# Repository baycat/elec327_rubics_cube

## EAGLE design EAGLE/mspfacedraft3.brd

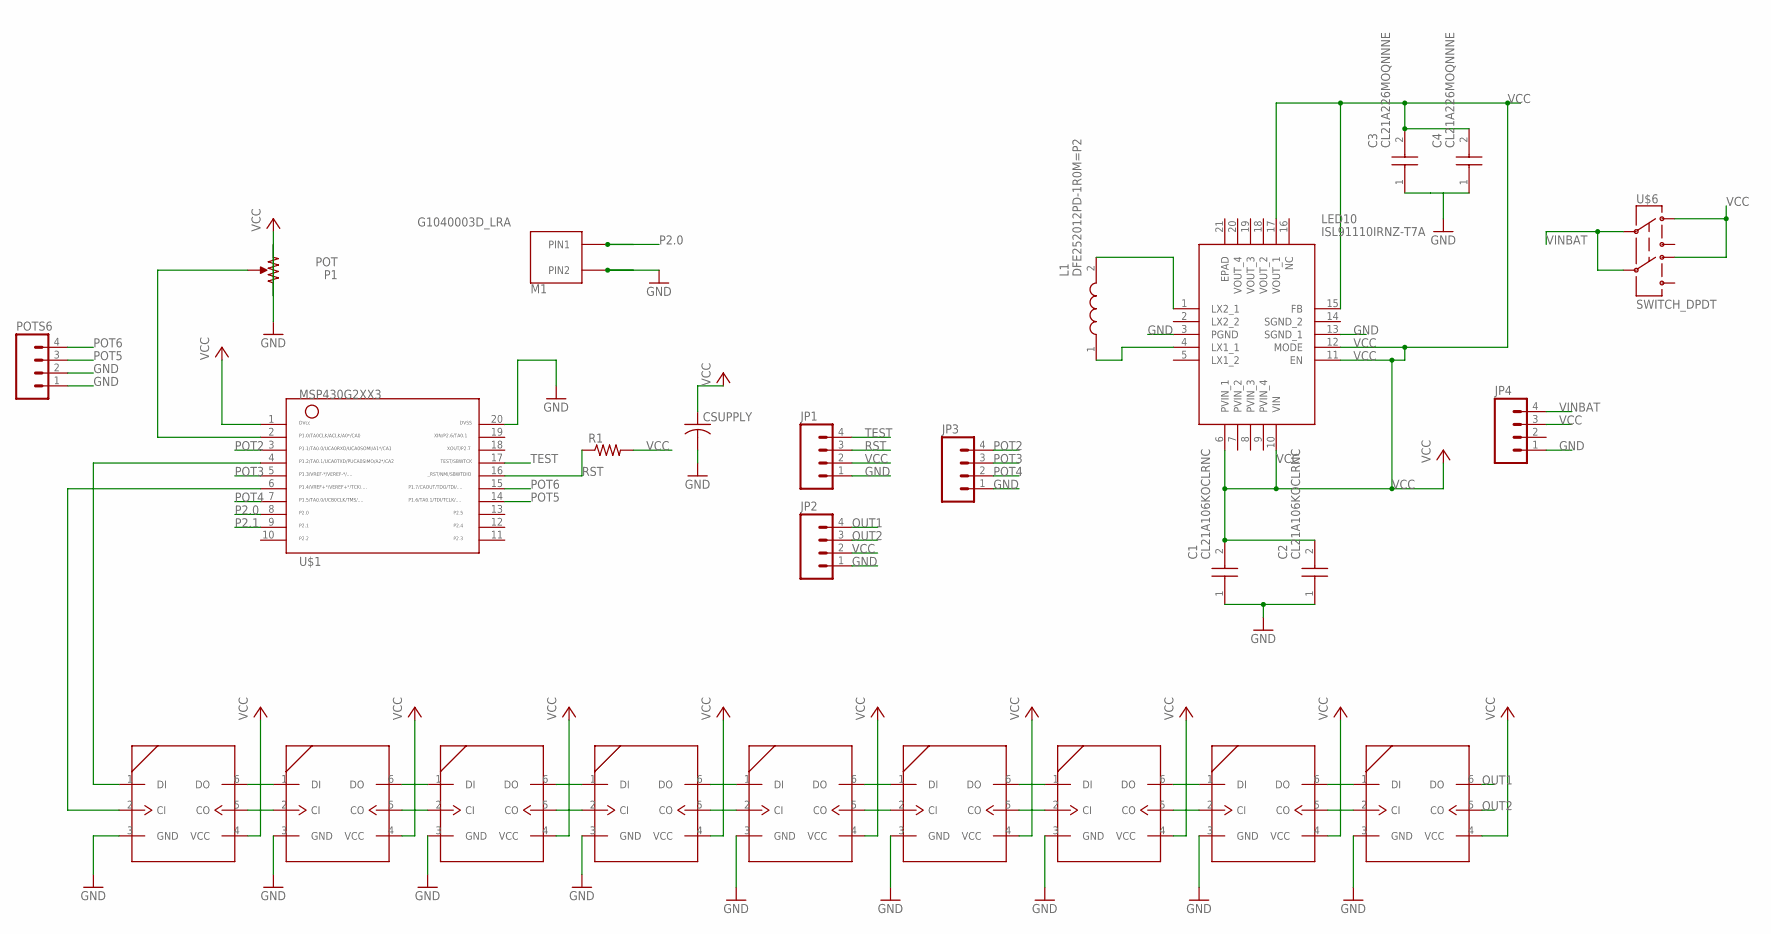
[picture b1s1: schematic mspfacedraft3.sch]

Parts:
C1, C2: CL21A106KOCLRNC; CAPC2012X95N
C3, C4: CL21A226MOQNNNE; CAPC2012X140N
CSUPPLY: C-USC1206; C1206
JP1, JP2, JP3, JP4: M04LOCK; 1X04_LOCK
L1: DFE252012PD-1R0M=P2; DFE2HCAH1R0MJ0L
LED1, LED2, LED3, LED4, LED5, LED6, LED7, LED8, LED9: APA102; 5050
LED10: ISL91110IRNZ-T7A; QFN50P400X400X100-21N
M1: G1040003D_LRA; COIN_VIBRATION_MOTOR
P1: POT
POTS6: M04LOCK; 1X04_LOCK
R1: R-US_R1206; R1206
U$1: MSP430G2XX3TSSOP; PW20
U$6: SWITCH_DPDT; JS_DPDT_TH

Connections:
GND: C1.1, C2.1, C3.1, C4.1, CSUPPLY.2, JP1.1, JP2.1, JP3.1, JP4.1, LED1.3 (GND), LED2.3 (GND), LED3.3 (GND), LED4.3 (GND), LED5.3 (GND), LED6.3 (GND), LED7.3 (GND), LED8.3 (GND), LED9.3 (GND), LED10.3 (PGND), LED10.13 (SGND_1), M1.P$2 (PIN2), P1.GND (CW), POTS6.1, POTS6.2, U$1.20
unnamed: LED1.6 (DO), LED2.1 (DI)
unnamed: LED1.5 (CO), LED2.2 (CI)
unnamed: LED2.6 (DO), LED3.1 (DI)
unnamed: LED2.5 (CO), LED3.2 (CI)
unnamed: LED3.6 (DO), LED4.1 (DI)
unnamed: LED3.5 (CO), LED4.2 (CI)
unnamed: LED1.1 (DI), U$1.4
unnamed: LED1.2 (CI), U$1.6
unnamed: LED4.6 (DO), LED5.1 (DI)
unnamed: LED4.5 (CO), LED5.2 (CI)
unnamed: LED5.6 (DO), LED6.1 (DI)
unnamed: LED5.5 (CO), LED6.2 (CI)
unnamed: LED6.6 (DO), LED7.1 (DI)
unnamed: LED6.5 (CO), LED7.2 (CI)
unnamed: LED7.6 (DO), LED8.1 (DI)
unnamed: LED7.5 (CO), LED8.2 (CI)
unnamed: LED8.6 (DO), LED9.1 (DI)
unnamed: LED8.5 (CO), LED9.2 (CI)
unnamed: L1.1, LED10.4 (LX1_1)
unnamed: P1.SIG (S), U$1.2
unnamed: L1.2, LED10.1 (LX2_1)
OUT1: JP2.4, LED9.6 (DO)
OUT2: JP2.3, LED9.5 (CO)
P2.0: M1.P$1 (PIN1), U$1.8
P2.1: U$1.9
POT2: JP3.4, U$1.3
POT3: JP3.3, U$1.5
POT4: JP3.2, U$1.7
POT5: POTS6.3, U$1.14
POT6: POTS6.4, U$1.15
RST: JP1.3, R1.1, U$1.16
TEST: JP1.4, U$1.17
VCC: C1.2, C2.2, C3.2, C4.2, CSUPPLY.1, JP1.2, JP2.2, JP4.3, LED1.4 (VCC), LED2.4 (VCC), LED3.4 (VCC), LED4.4 (VCC), LED5.4 (VCC), LED6.4 (VCC), LED7.4 (VCC), LED8.4 (VCC), LED9.4 (VCC), LED10.6 (PVIN_1), LED10.10 (VIN), LED10.11 (EN), LED10.12 (MODE), LED10.15 (FB), LED10.17 (VOUT_1), P1.VDD (CCW), R1.2, U$1.1, U$6.1, U$6.4
VINBAT: JP4.4, U$6.2, U$6.5

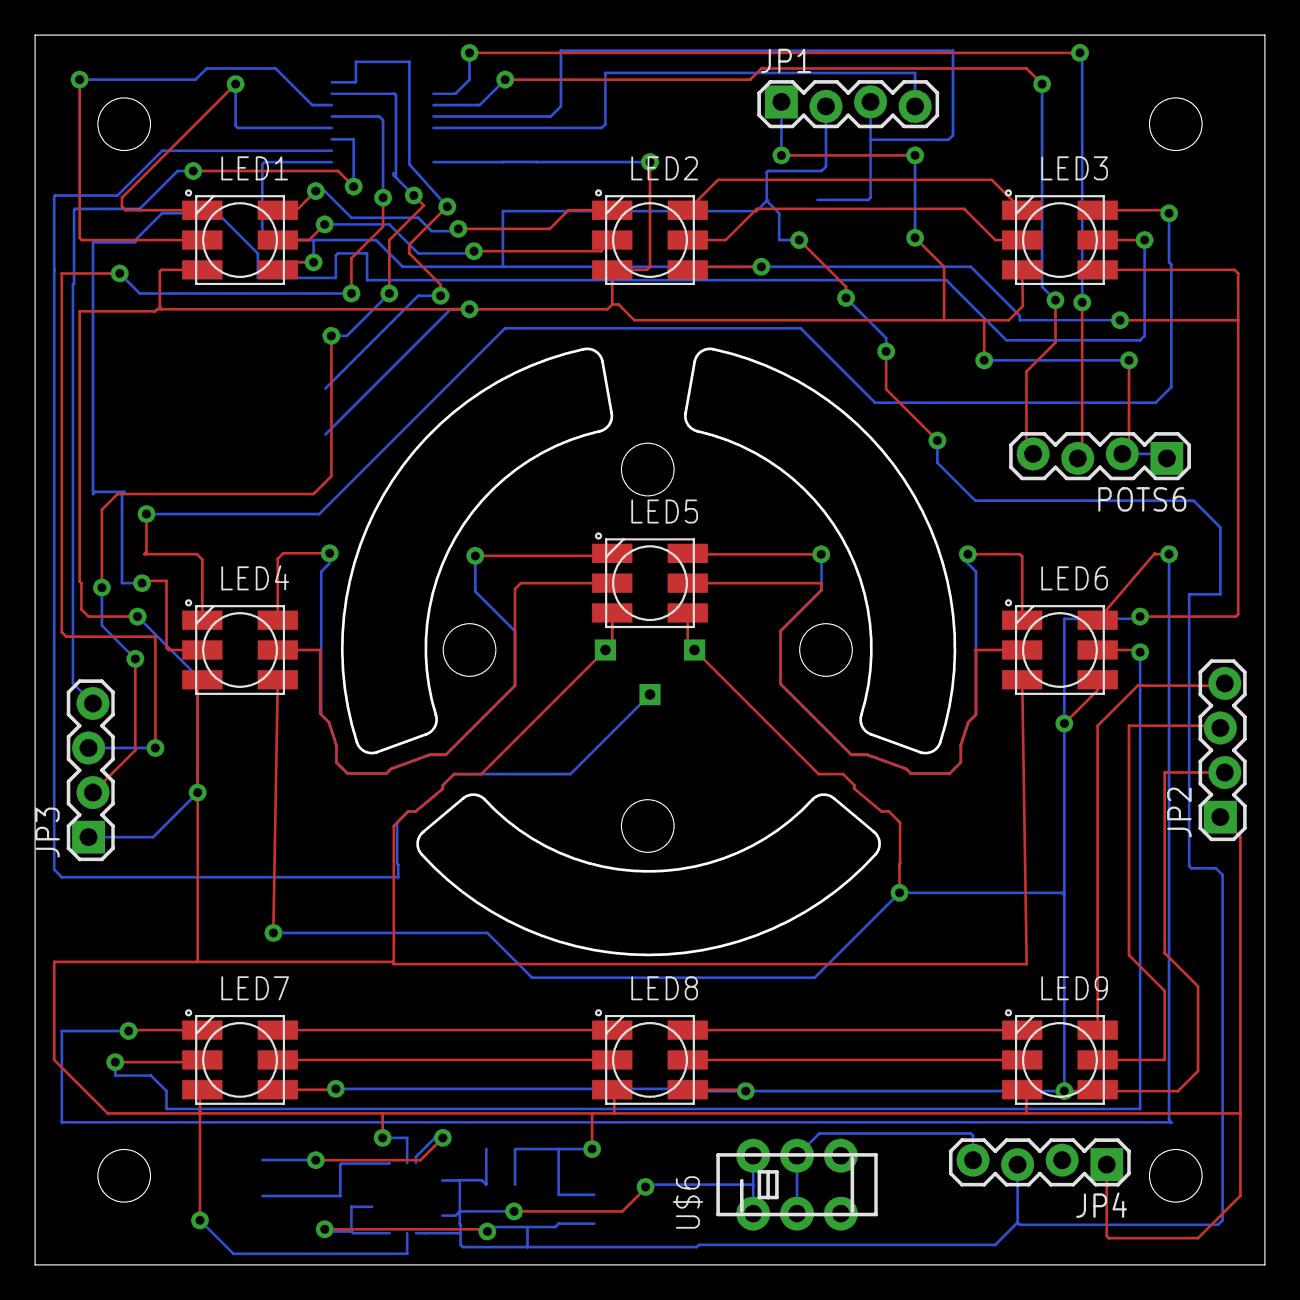
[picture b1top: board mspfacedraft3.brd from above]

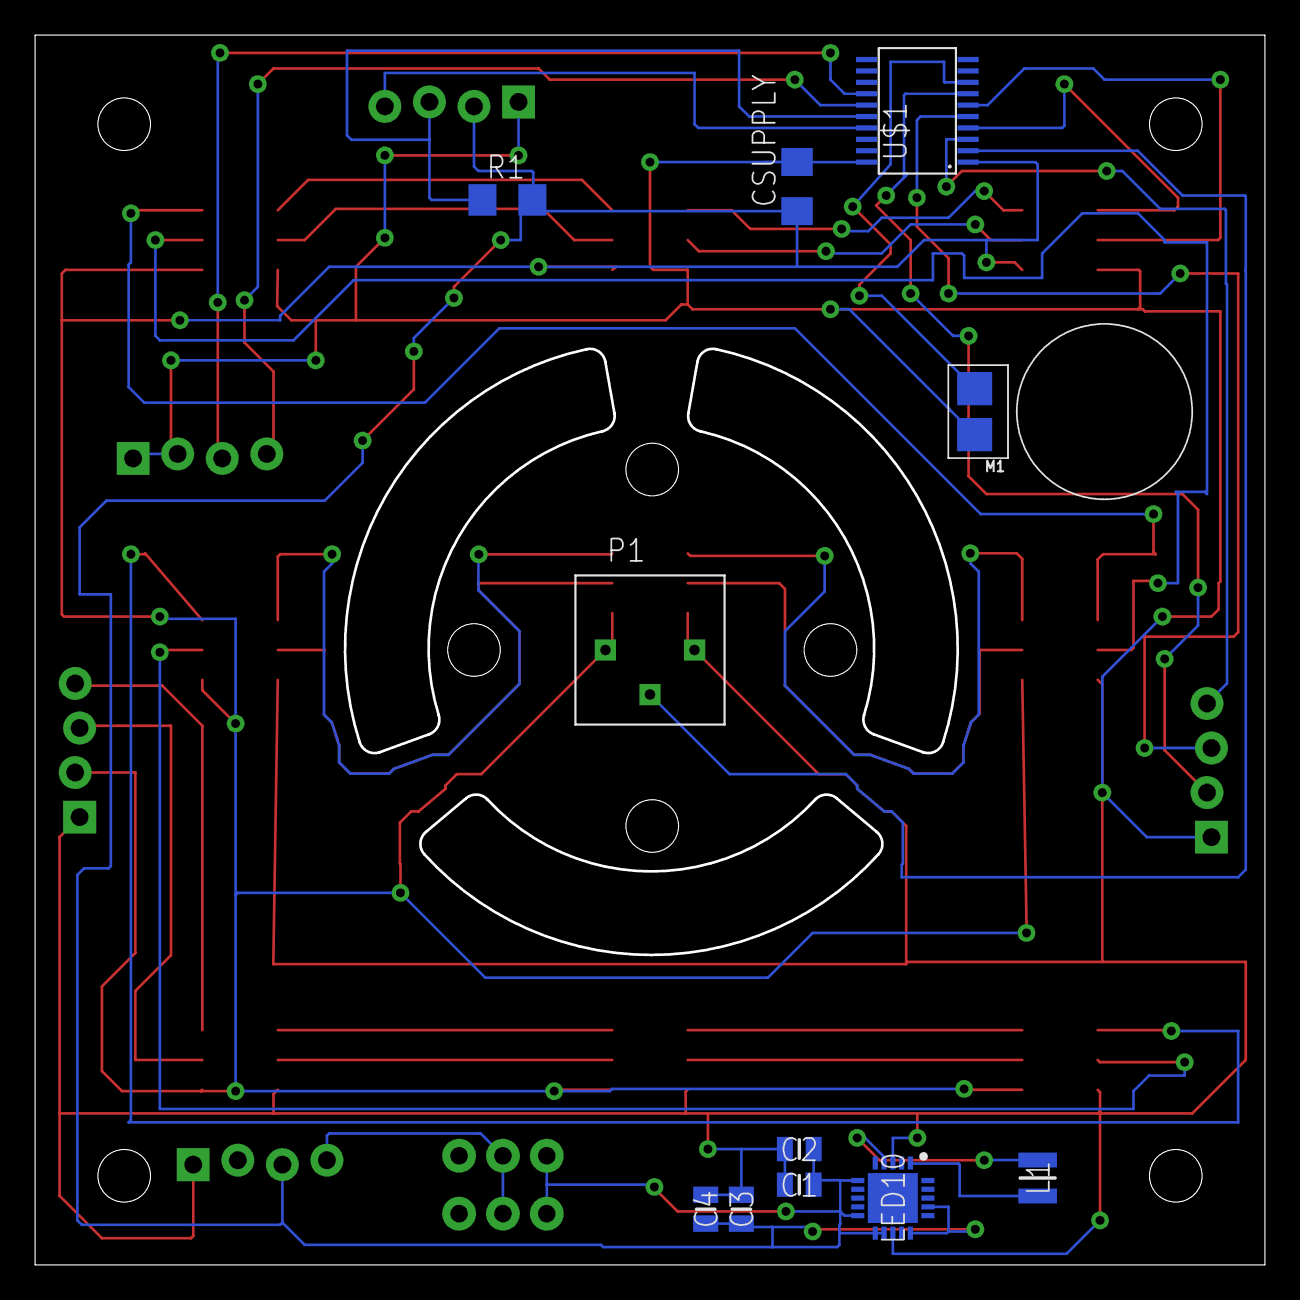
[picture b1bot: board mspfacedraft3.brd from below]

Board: 2 copper layers, 70.1 x 70.1 mm, 26 parts (11 on the bottom side), 34 nets.

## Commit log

2022-04-08 CAD Files
2022-04-08 more cad
2022-04-08 cad update
2022-04-10 starting to add code files
2022-04-10 fixed file formats
2022-04-10 added file for sound
2022-04-10 added file for scrambling cube and file for checking for scramble from gyro input
2022-04-10 cad updates ' git push
2022-04-10 outlining code needs throughout files
2022-04-10 added header files
2022-04-10 added inputs and outputs for functions to further outline logic
2022-04-10 libr for potentiometer
2022-04-11 test board file added
2022-04-17 added picture of spring potentiometer bottom
2022-04-18 msp face file v2 added
2022-04-18 Added msp face v3 pcb
2022-04-19 libr for voltage regulator parts
2022-04-19 Schematic/brd updates/fixes
2022-04-22 Added non msp face eagle cad
2022-04-22 Create rotationLogic.c
    function doesnt quite work yet when called in main (fix needed)
2022-04-22 Create LEDinterface.c
    need to expand to include all faces
2022-04-23 final PCB files and output files
2022-05-01 adc read code ex
2022-05-01 base random code
2022-05-01 got rid of scramble check due to decided way to scramble
2022-05-01 set up rand for move parameters
2022-05-02 scramble function
2022-05-02 initialize random
2022-05-03 trying to move turning logic to turn.c
2022-05-03 more turn changes
2022-05-03 trying to implement turn code
2022-05-03 scramble h
2022-05-04 added code to debug hardware
2022-05-04 no noise
2022-05-04 random cw and ccw
2022-05-04 scramble rand
2022-05-04 scramble

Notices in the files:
parts and their libraries:
SparkFun: Licensing: CC v3.0 Share-Alike You are welcome to use this library for commercial purposes.
